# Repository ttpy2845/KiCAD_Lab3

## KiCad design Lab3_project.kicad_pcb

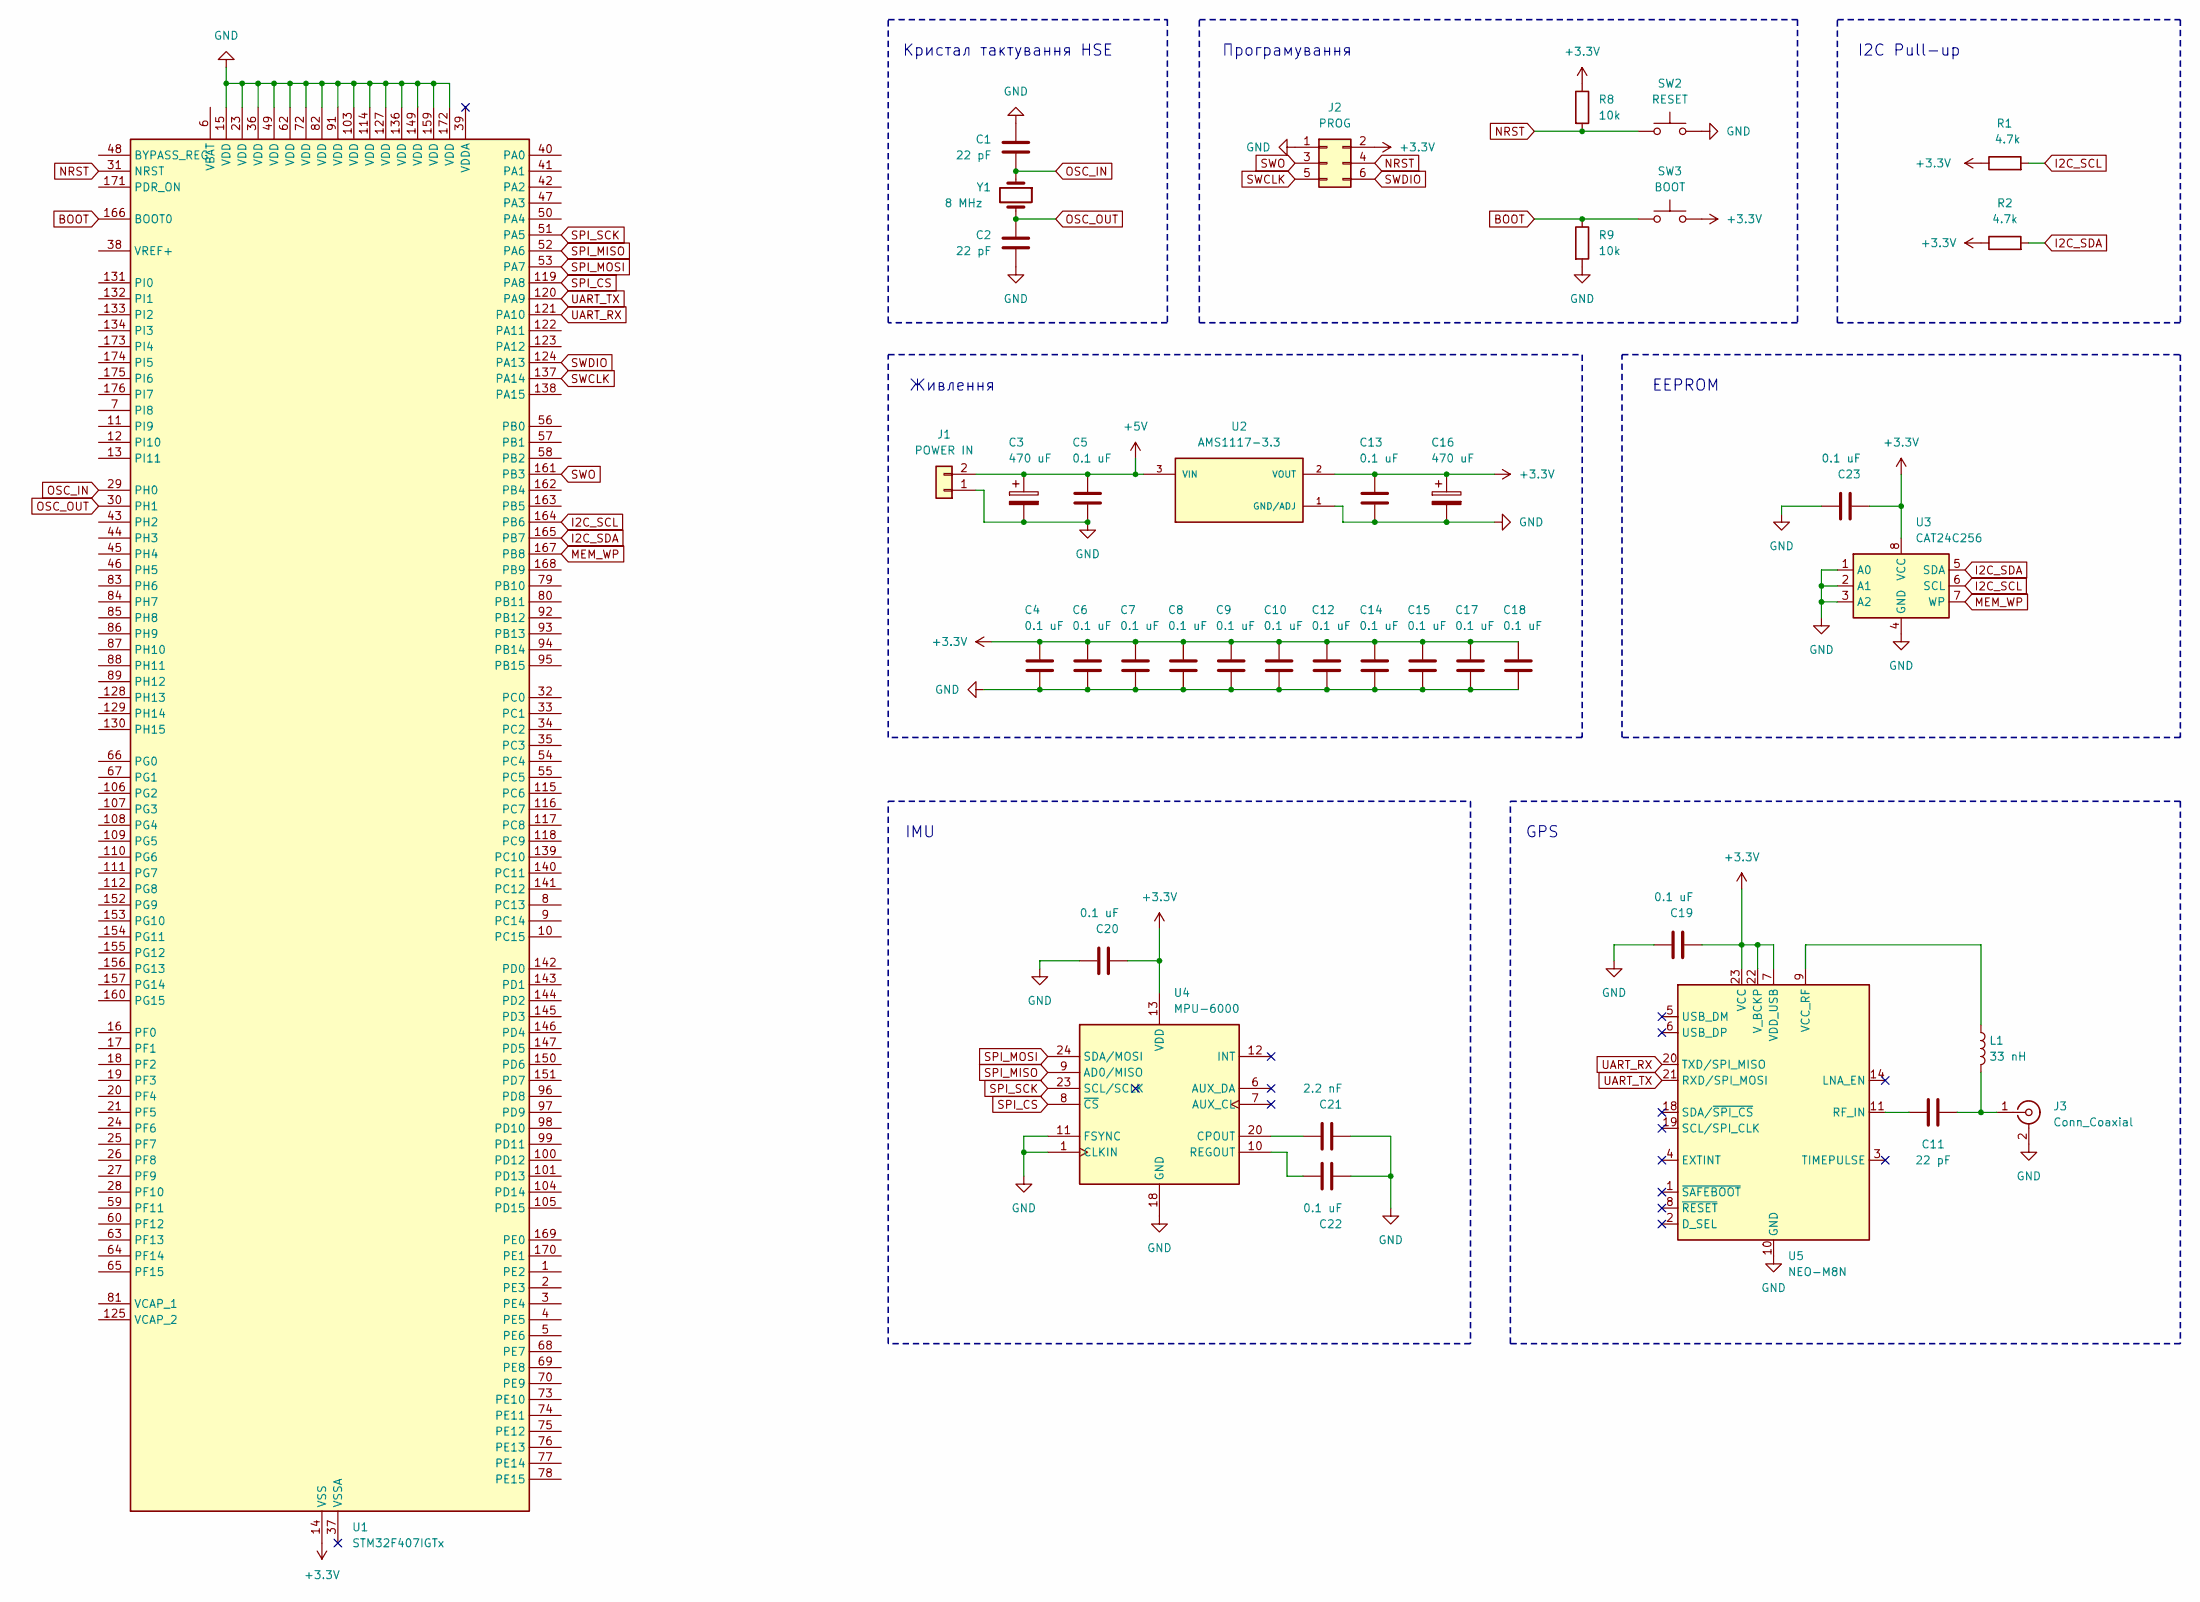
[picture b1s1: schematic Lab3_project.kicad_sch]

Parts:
C1, C2: 22 pF; C_1206_3216Metric_Pad1.33x1.80mm_HandSolder
C3, C16: 470 uF; CP_Radial_D8.0mm_P3.80mm
C4, C6, C7, C8, C9, C10, C12, C14, C15, C17, C18, C19, C20, C22, C23: 0.1 uF; C_0805_2012Metric_Pad1.18x1.45mm_HandSolder
C5, C13: 0.1 uF; C_1206_3216Metric_Pad1.33x1.80mm_HandSolder
C11: 22 pF; C_0805_2012Metric_Pad1.18x1.45mm_HandSolder
C21: 2.2 nF; C_0805_2012Metric_Pad1.18x1.45mm_HandSolder
J1: POWER IN; JST_XH_B2B-XH-A_1x02_P2.50mm_Vertical
J2: PROG; PinHeader_2x03_P2.54mm_Vertical
J3: Conn_Coaxial; SMA_Molex_73251-1153_EdgeMount_Horizontal
L1: 33 nH; L_0805_2012Metric_Pad1.15x1.40mm_HandSolder
R1, R2: 4.7k; R_1206_3216Metric_Pad1.30x1.75mm_HandSolder
R8, R9: 10k; R_1206_3216Metric_Pad1.30x1.75mm_HandSolder
SW2: RESET; SW_PUSH_6mm_H5mm
SW3: BOOT; SW_PUSH_6mm_H5mm
U1: STM32F407IGTx; LQFP-176_24x24mm_P0.5mm
U2: AMS1117-3.3; SOT-223-3_TabPin2; PARTREV N/A
U3: CAT24C256; SOIC-8_3.9x4.9mm_P1.27mm
U4: MPU-6000; InvenSense_QFN-24_4x4mm_P0.5mm
U5: NEO-M8N; ublox_NEO
Y1: 8 MHz; Crystal_HC18-U_Vertical

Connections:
+3.3V: C4.1, C6.1, C7.1, C8.1, C9.1, C10.1, C12.1, C13.1, C14.1, C15.1, C16.1, C17.1, C18.1, C19.2, C20.2, C23.2, J2.2, R1.1, R2.1, R8.1, SW3.2, U1.14 (VSS), U1.22 (VSS), U1.61 (VSS), U1.71 (VSS), U1.90 (VSS), U1.102 (VSS), U1.113 (VSS), U1.126 (VSS), U1.135 (VSS), U1.148 (VSS), U1.158 (VSS), U2.2 (VOUT), U3.8 (VCC), U4.13 (VDD), U5.7 (VDD_USB), U5.22 (V_BCKP), U5.23 (VCC)
+5V: C3.1, C5.1, J1.2, U2.3 (VIN)
BOOT: R9.1, SW3.1, U1.166 (BOOT0)
GND: C1.1, C2.2, C3.2, C4.2, C5.2, C6.2, C7.2, C8.2, C9.2, C10.2, C12.2, C13.2, C14.2, C15.2, C16.2, C17.2, C18.2, C19.1, C20.1, C21.2, C22.2, C23.1, J1.1, J2.1, J3.2 (Ext), R9.2, SW2.2, U1.15 (VDD), U1.23 (VDD), U1.36 (VDD), U1.49 (VDD), U1.62 (VDD), U1.72 (VDD), U1.82 (VDD), U1.91 (VDD), U1.103 (VDD), U1.114 (VDD), U1.127 (VDD), U1.136 (VDD), U1.149 (VDD), U1.159 (VDD), U1.172 (VDD), U2.1 (GND/ADJ), U3.1 (A0), U3.2 (A1), U3.3 (A2), U3.4 (GND), U4.1 (CLKIN), U4.11 (FSYNC), U4.18 (GND), U5.10 (GND), U5.12 (GND), U5.13 (GND), U5.24 (GND)
I2C_SCL: R1.2, U1.164 (PB6), U3.6 (SCL)
I2C_SDA: R2.2, U1.165 (PB7), U3.5 (SDA)
MEM_WP: U1.167 (PB8), U3.7 (WP)
NRST: J2.4, R8.2, SW2.1, U1.31 (NRST)
unnamed: C11.2, J3.1 (In), L1.2
unnamed: C21.1, U4.20 (CPOUT)
unnamed: C22.1, U4.10 (REGOUT)
unnamed: C11.1, U5.11 (RF_IN)
unnamed: L1.1, U5.9 (VCC_RF)
OSC_IN: C1.2, U1.29 (PH0), Y1.1
OSC_OUT: C2.1, U1.30 (PH1), Y1.2
SPI_CS: U1.119 (PA8), U4.8 (~CS)
SPI_MISO: U1.52 (PA6), U4.9 (AD0/MISO)
SPI_MOSI: U1.53 (PA7), U4.24 (SDA/MOSI)
SPI_SCK: U1.51 (PA5), U4.23 (SCL/SCLK)
SWCLK: J2.5, U1.137 (PA14)
SWDIO: J2.6, U1.124 (PA13)
SWO: J2.3, U1.161 (PB3)
UART_RX: U1.121 (PA10), U5.20 (TXD/SPI_MISO)
UART_TX: U1.120 (PA9), U5.21 (RXD/SPI_MOSI)

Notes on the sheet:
I2C Pull-up
EEPROM
GPS
Живлення
Програмування
IMU
Кристал тактування HSE

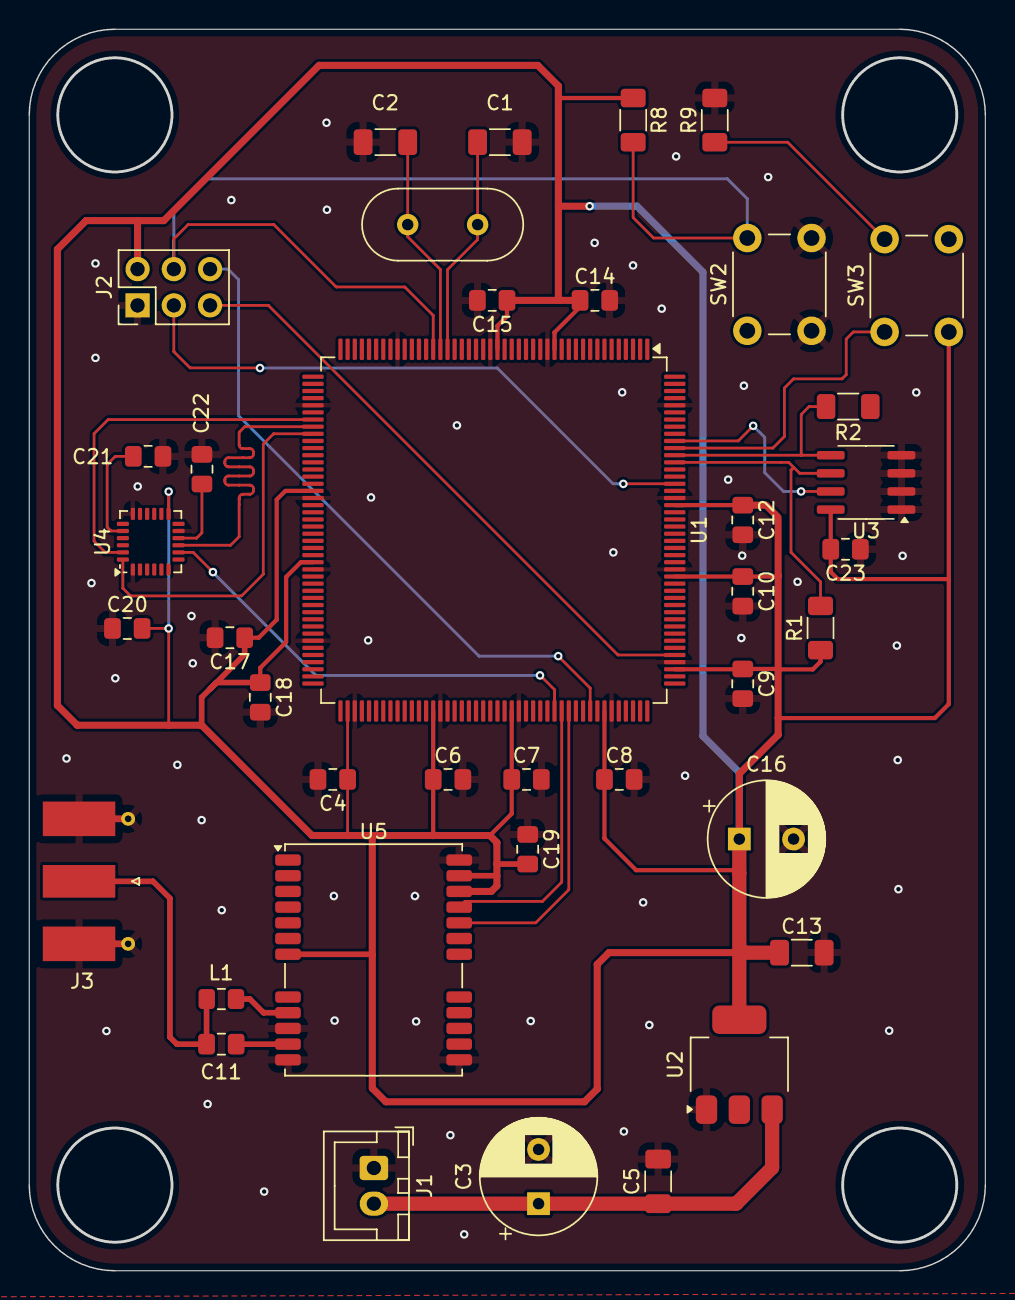
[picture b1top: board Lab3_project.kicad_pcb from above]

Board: 2 copper layers, 66.9 x 86.9 mm, 39 parts (0 on the bottom side), 24 nets.

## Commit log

2026-04-17 Init commit
2026-04-17 Complete scheme, add footprints
2026-04-20 Trace route
2026-04-29 fix gnd zone
2026-04-29 точно останній
